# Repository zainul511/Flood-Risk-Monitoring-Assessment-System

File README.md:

# Flood Early Warning System

An IoT-based flood early warning system using ESP32 and wireless communication to monitor real-time water levels, generate alerts, and provide live dashboard visualization.

---

## Abstract
This project implements a real-time Flood Early Warning System using ESP32-based sensor nodes and a centralized controller unit. Water level data is measured using ultrasonic sensors and transmitted wirelessly using ESP-NOW. The controller unit evaluates risk levels, generates visual and audible alerts, and hosts a real-time web dashboard for monitoring.

---

## Problem Statement
Flood disasters often occur due to the absence of real-time, localized monitoring and early warning mechanisms. A low-cost, scalable, and wireless solution is required to provide timely flood alerts based on actual water level measurements.

---

## Objectives
- To design a real-time flood monitoring system using IoT
- To acquire water level data from remote locations
- To transmit data wirelessly with low latency
- To evaluate flood risk levels centrally
- To provide real-time alerts and dashboard visualization

---

## Features
- Real-time water level sensing
- ESP-NOW based low-latency wireless communication
- Centralized controller with alert logic
- LED and buzzer based warning system
- Live web-based monitoring dashboard
- Modular design scalable to multiple sensor nodes
- Custom-designed PCBs and enclosures

---

## System Overview
The system consists of:
- **Data Unit (Transmitter):** Measures water level and sends data wirelessly  
- **Controller Unit (Receiver):** Receives data, evaluates risk, triggers alerts, and hosts the dashboard  

---

## Hardware Used

### Controller Unit
- ESP32-C3 microcontroller
- LED indicators (Safe / Warning / Danger)
- Buzzer for audible alerts
- Power management and battery charging circuit
- Custom PCB and enclosure

### Data Unit (Sub-Unit)
- ESP32 microcontroller
- Ultrasonic water level sensor (HC-SR04 type)
- Power management and battery charging circuit
- Custom PCB and enclosure

---

## Firmware

### Communication Protocol
- **ESP-NOW** for sensor data transmission
- Fixed Wi-Fi channel for reliable communication
- One-to-one communication (extendable to multi-node)

### Transmitter (Data Unit)
- Measures water level using ultrasonic sensor
- Sends distance data periodically via ESP-NOW

**Libraries Used:**
- `WiFi.h`
- `esp_now.h`
- `esp_wifi.h`

### Receiver (Controller Unit)
- Receives sensor data via ESP-NOW
- Determines flood risk level
- Controls LEDs and buzzer
- Hosts a real-time web dashboard

**Libraries Used:**
- `WiFi.h`
- `esp_now.h`
- `esp_wifi.h`
- `WebServer.h`

---

## How It Works
1. The data unit measures water level using an ultrasonic sensor  
2. Measured distance is transmitted wirelessly via ESP-NOW  
3. The controller unit receives the data and evaluates risk levels  
4. LEDs and buzzer indicate Safe, Warning, or Danger conditions  
5. A web dashboard displays real-time distance and alert status  

---

## Real-Time Dashboard
The controller unit hosts a built-in web server that provides:
- Live water level display
- Flood status indication (Safe / Warning / Danger)
- Real-time distance trend graph

---

## Getting Started

### Prerequisites
- Arduino IDE
- ESP32 board package installed
- Two ESP32 boards (Data Unit & Controller Unit)

### Steps
1. Clone this repository
2. Upload `data_unit.ino` to the data unit ESP32
3. Upload `controller_unit.ino` to the controller unit ESP32
4. Configure Wi-Fi credentials in the controller firmware
5. Power both units
6. Access the dashboard using the controller’s IP address

---

## Demonstration
The system was successfully demonstrated by sensing real-time water level changes, transmitting data wirelessly, visualizing data on a live dashboard, and generating alerts based on predefined thresholds.

---

## Applications
- Flood early warning systems
- Disaster management
- Smart water monitoring
- Environmental sensing networks

---

## License
This project is licensed under the **MIT License**.

## Contributors

- [Ahamed Hathi](https://github.com/ahamedhathi2002-ux)
- [Zainul Hussain](https://github.com/zainul511)
- [Mohomed Sahmi](https://github.com/sahmi344)

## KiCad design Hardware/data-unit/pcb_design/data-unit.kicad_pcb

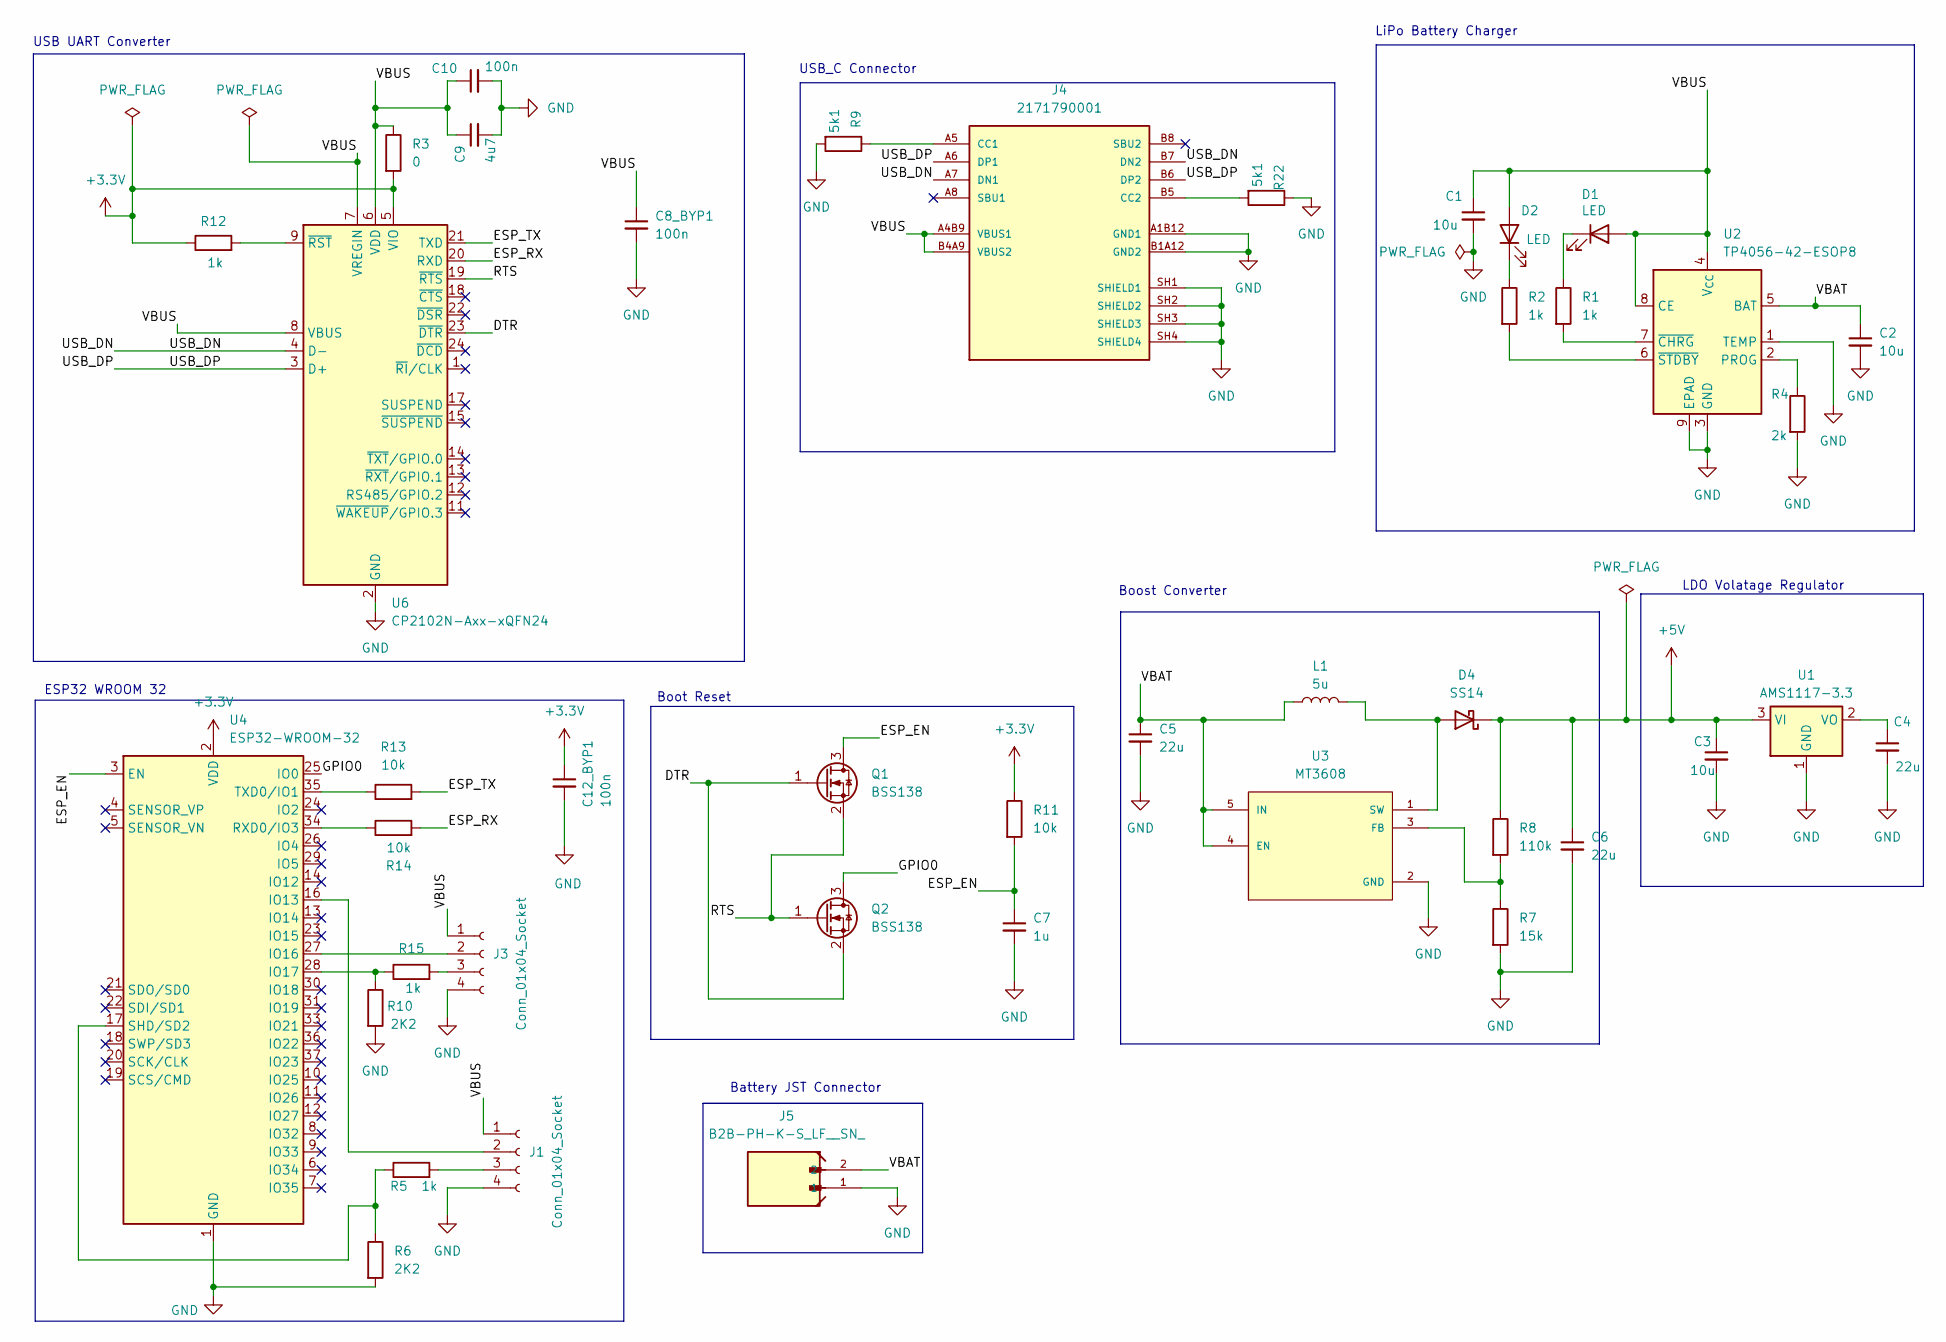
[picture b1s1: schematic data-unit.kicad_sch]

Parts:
C1, C2, C3: 10u; C_0805_2012Metric
C4, C5, C6: 22u; C_0805_2012Metric
C7: 1u; C_0805_2012Metric
C8_BYP1, C10, C12_BYP1: 100n; C_0805_2012Metric
C9: 4u7; C_0805_2012Metric
D1, D2: LED; LED_0805_2012Metric
D4: SS14; D_SMA
J1, J3: Conn_01x04_Socket; PinSocket_1x04_P2.00mm_Horizontal
J4: 2171790001; MOLEX_2171790001; PARTREV A1
J5: B2B-PH-K-S_LF__SN_; JST_B2B-PH-K-S_LF__SN_
L1: 5u; L_0805_2012Metric
Q1, Q2: BSS138; SOT-23
R1, R2, R5, R12, R15: 1k; R_0805_2012Metric
R3: 0; R_0805_2012Metric
R4: 2k; R_0805_2012Metric
R6, R10: 2K2; R_0805_2012Metric
R7: 15k; R_0805_2012Metric
R8: 110k; R_0805_2012Metric
R9, R22: 5k1; R_0805_2012Metric
R11, R13, R14: 10k; R_0805_2012Metric
U1: AMS1117-3.3; SOT-223-3_TabPin2
U2: TP4056-42-ESOP8; SOIC-8-1EP_3.9x4.9mm_P1.27mm_EP2.41x3.3mm_ThermalVias
U3: MT3608; SOT95P280X145-6N; PARTREV 1.0
U4: ESP32-WROOM-32
U6: CP2102N-Axx-xQFN24; QFN-24-1EP_4x4mm_P0.5mm_EP2.6x2.6mm

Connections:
+3.3V: C12_BYP1.1, R3.2, R11.1, R12.1, U4.2 (VDD), U6.5 (VIO)
+5V: C3.1, C6.1, D4.1 (K), R8.1, U1.3 (VI)
/DTR: Q1.1 (G), Q2.2 (S), U6.23 (~DTR)
/ESP_EN: C7.1, Q1.3 (D), R11.2, U4.3 (EN)
/ESP_RX: R14.2, U6.20 (RXD)
/ESP_TX: R13.2, U6.21 (TXD)
/GPIO0: Q2.3 (D), U4.25 (IO0)
/RTS: Q1.2 (S), Q2.1 (G), U6.19 (~RTS)
/USB_DN: J4.A7 (DN1), J4.B7 (DN2), U6.4 (D-)
/USB_DP: J4.A6 (DP1), J4.B6 (DP2), U6.3 (D+)
/VBAT: C2.1, C5.1, J5.2, L1.1, U2.5 (BAT), U3.4 (EN), U3.5 (IN)
/VBUS: C1.1, C8_BYP1.1, C9.1, C10.1, D1.2 (A), D2.2 (A), J1.1, J3.1, J4.A4B9 (VBUS1), J4.B4A9 (VBUS2), R3.1, U2.4 (V_{CC}), U2.8 (CE), U6.6 (VDD), U6.7 (VREGIN), U6.8 (VBUS)
GND: C1.2, C2.2, C3.2, C4.2, C5.2, C6.2, C7.2, C8_BYP1.2, C9.2, C10.2, C12_BYP1.2, J1.4, J3.4, J4.A1B12 (GND1), J4.B1A12 (GND2), J4.SH1 (SHIELD1), J4.SH2 (SHIELD2), J4.SH3 (SHIELD3), J4.SH4 (SHIELD4), J5.1, R4.2, R6.2, R7.2, R9.2, R10.2, R22.1, U1.1 (GND), U2.1 (TEMP), U2.3 (GND), U2.9 (EPAD), U3.2 (GND), U4.1 (GND), U4.15 (GND), U4.38 (GND), U4.39 (GND), U6.2 (GND), U6.25 (GND)
unnamed: D1.1 (K), R1.1
unnamed: D2.1 (K), R2.1
unnamed: D4.2 (A), L1.2, U3.1 (SW)
unnamed: J1.2, U4.16 (IO13)
unnamed: J1.3, R5.2
unnamed: J3.2, U4.27 (IO16)
unnamed: J3.3, R15.2
unnamed: J4.A5 (CC1), R9.1
unnamed: J4.B5 (CC2), R22.2
unnamed: C4.1, U1.2 (VO)
unnamed: R4.1, U2.2 (PROG)
unnamed: R1.2, U2.7 (~CHRG)
unnamed: R2.2, U2.6 (~STDBY)
unnamed: R7.1, R8.2, U3.3 (FB)
unnamed: R10.1, R15.1, U4.28 (IO17)
unnamed: R14.1, U4.34 (RXD0/IO3)
unnamed: R5.1, R6.1, U4.17 (SHD/SD2)
unnamed: R13.1, U4.35 (TXD0/IO1)
unnamed: R12.2, U6.9 (~RST)

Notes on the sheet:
Boot Reset
USB UART Converter
ESP32 WROOM 32
USB_C Connector
LiPo Battery Charger
Battery JST Connector
Boost Converter
LDO Volatage Regulator

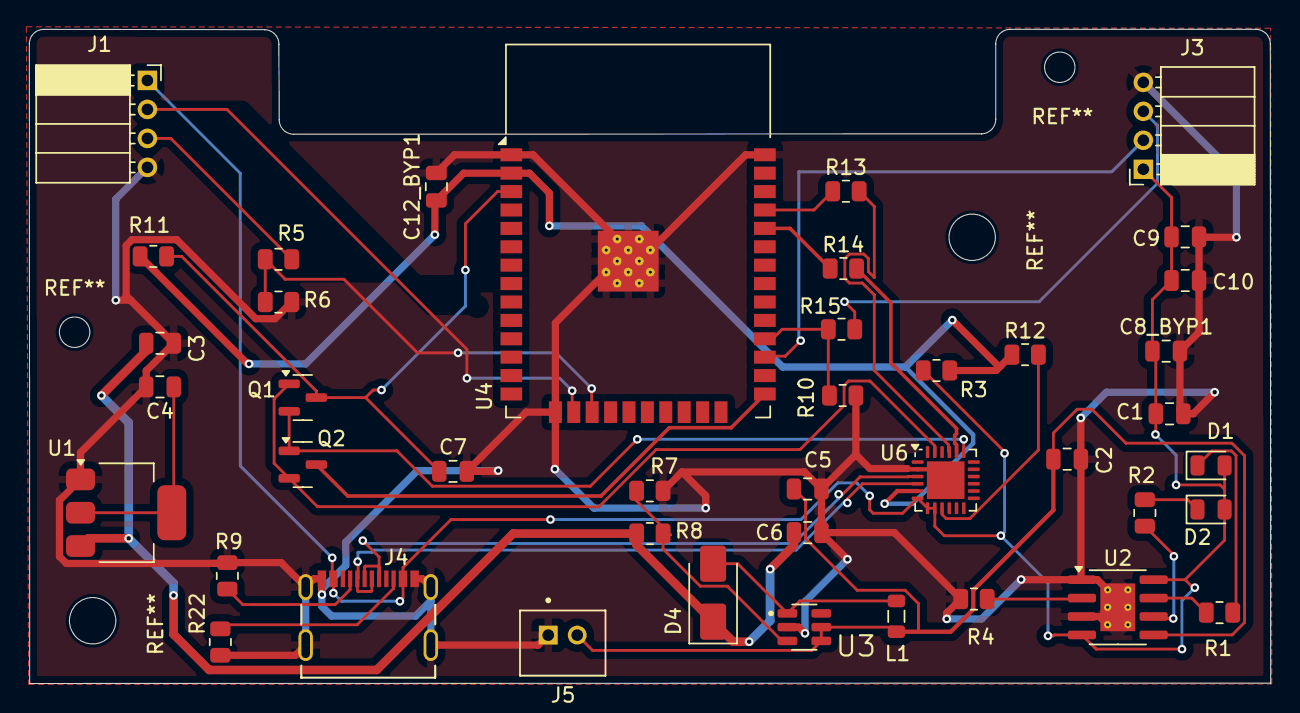
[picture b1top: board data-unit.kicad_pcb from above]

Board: 2 copper layers, 85.7 x 45.1 mm, 42 parts (0 on the bottom side), 32 nets.

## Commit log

2026-01-19 Initial Commit.
2026-01-19 Revise README for Flood Early Warning System
    Updated project title and description for clarity. Added sections on abstract, problem statement, objectives, features, system overview, hardware used, firmware details, operation steps, demonstratio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
2026-01-19 Add contributors section to README
    Added a contributors section with names and links.
2026-01-30 Update contributor link for Mohomed Sahmi
